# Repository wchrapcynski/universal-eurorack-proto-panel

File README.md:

# 8HP Eurorack Proto Panel

An open-hardware, all-in-one 8HP Eurorack front-panel PCB designed for
solderless breadboard synth prototyping. Front-panel controls (pots, jacks,
switch, button, and LEDs) mount directly to the front of the PCB and break out
to labeled 2.54 mm (0.1 in) female headers on the back for quick jumper-wire
connections to a BusBoard BB400 breadboard.

Designed as the companion panel to the
[BB400 Eurorack Power Breakout](https://github.com/wchrapcynski/bb400-euro-power).

## Status

**v0.1** - Initial PCB revision complete (ERC and DRC clean). Awaiting physical
fabrication and hardware verification.

## Features

- **Standard 8HP Eurorack size:** 40.3 x 128.5 mm with Doepfer A-100 mounting
  holes (`H1`-`H4`)
- **All-in-one PCB faceplate:** No separate aluminum panel required
- **All through-hole (THT) assembly:** Beginner-friendly hand soldering
- **Clean 2-layer layout:** All signal routing on `F.Cu` with an unbroken `GND`
  ground plane on `B.Cu`
- **Labeled rear breakout headers:** `J5`, `J6`, and `J7` clearly marked on the
  back silkscreen so you can patch to a breadboard without checking the
  schematic
- **Breadboard sled mounts:** Two centered M3 holes (`H5`, `H6`) for bolting a
  perpendicular 3D-printed BB400 breadboard sled behind the panel

## Front Panel Controls

- 3x 100kB vertical 9 mm trimmer potentiometers (`RV1`-`RV3`)
- 4x 3.5 mm mono jacks (`J1`-`J4`, Thonkiconn / PJ398SM)
- 1x SPDT slide switch (`SW1`)
- 1x 6 mm momentary tactile push button (`SW2`)
- 2x 3 mm indicator LEDs (`D1`, `D2`) with built-in 2.2k current-limiting
  resistors (`R1`, `R2`) on the back

## Rear Header Pinout (`B.Cu`)

All breakout headers are 2.54 mm pitch vertical female sockets mounted on the
back of the board.

### `J5` (1x9 - Potentiometers)

| Pin | Net  | Description          |
|-----|------|----------------------|
| 1   | P1_1 | RV1 pin 1            |
| 2   | P1_W | RV1 wiper (pin 2)    |
| 3   | P1_3 | RV1 pin 3            |
| 4   | P2_1 | RV2 pin 1            |
| 5   | P2_W | RV2 wiper (pin 2)    |
| 6   | P2_3 | RV2 pin 3            |
| 7   | P3_1 | RV3 pin 1            |
| 8   | P3_W | RV3 wiper (pin 2)    |
| 9   | P3_3 | RV3 pin 3            |

### `J6` (1x7 - Switch, Button, LEDs)

| Pin | Net     | Description                            |
|-----|---------|----------------------------------------|
| 1   | SW1_A   | SPDT switch throw A                    |
| 2   | SW1_C   | SPDT switch common                     |
| 3   | SW1_B   | SPDT switch throw B                    |
| 4   | BTN_1   | Tactile button side 1                  |
| 5   | BTN_2   | Tactile button side 2                  |
| 6   | LED1_IN | LED D1 input (via 2.2k R1 to D1 -> GND)|
| 7   | LED2_IN | LED D2 input (via 2.2k R2 to D2 -> GND)|

### `J7` (1x6 - Jacks and Ground)

| Pin | Net    | Description      |
|-----|--------|------------------|
| 1   | J1_TIP | Jack J1 tip      |
| 2   | J2_TIP | Jack J2 tip      |
| 3   | J3_TIP | Jack J3 tip      |
| 4   | J4_TIP | Jack J4 tip      |
| 5   | GND    | Ground reference |
| 6   | GND    | Ground reference |

## Bill of Materials (BOM)

[Interactive BOM](https://wchrapcynski.github.io/universal-eurorack-proto-panel/bom/ibom.html)

| Ref     | Qty | Value / Part          | Footprint / Notes                                              |
|---------|-----|-----------------------|----------------------------------------------------------------|
| RV1-RV3 | 3   | 100kB                 | 9 mm vertical tall trimmer pot (Bourns PTV09A-1 compatible)    |
| J1-J4   | 4   | 3.5 mm mono jack      | QingPu WQP-PJ398SM (Thonkiconn), vertical                      |
| SW1     | 1   | SPDT slide switch     | C&K OS102011MS2Q (2.0 mm pin pitch, straight THT)              |
| SW2     | 1   | Tactile push button   | 6 x 6 mm standard 4-pin THT push button                        |
| D1, D2  | 2   | 3 mm LED              | Standard 3 mm THT LED (any color)                              |
| R1, R2  | 2   | 2.2k                  | 1/4W axial resistor, 7.62 mm pitch (mounted on back)           |
| J5      | 1   | 1x9 female header     | 2.54 mm vertical pin socket (mounted on back)                  |
| J6      | 1   | 1x7 female header     | 2.54 mm vertical pin socket (mounted on back)                  |
| J7      | 1   | 1x6 female header     | 2.54 mm vertical pin socket (mounted on back)                  |

## Fabrication

- Designed in **KiCad 10**
- 2-layer PCB, 1.6 mm FR-4, 1 oz copper
- Dimensions: 40.3 x 128.5 mm (8HP)
- Can be ordered directly from OSH Park by uploading the `.kicad_pcb` file, or
  fabricated anywhere using standard Gerber + drill exports

## 3D-Printed BB400 Breadboard Sled

The repository includes a perpendicular breadboard sled that bolts to the back
of the PCB at `H5` and `H6` (`98.0 mm` apart) and holds a BusBoard BB400
(`84 x 54 x 9 mm`) cleanly inside the 8HP width and 3U rail clearance.

### Files

- `baseplate.FCStd` - FreeCAD 1.1 source file
- `baseplate.stl` - Ready-to-slice 3D-printable STL

### Dimensions and Printing

- **Size:** 65 mm deep x 106 mm tall x 3 mm thick wall (24 mm total width with
  mounting tabs)
- **Clearances:** 5 mm front recess between the two tabs clears `R1` and rear
  solder joints; 65 mm depth leaves room for `J5` jumper wires while fitting
  inside shallow cases (tested against a 70 mm deep Apache 2800 Eurorack case)
- **Orientation:** Print flat on the build plate (tabs pointing up), **no
  supports required**
- **Hardware:** 2x M3 screws (8 mm or 10 mm) and 2x standard M3 hex nuts
  (press-fit into the rear 2.6 mm hex pockets)

## License

Copyright (c) 2026 William Chrapcynski

This hardware design is licensed under the Creative Commons
Attribution-NonCommercial-ShareAlike 4.0 International License
(**CC BY-NC-SA 4.0**). See https://creativecommons.org/licenses/by-nc-sa/4.0/
for details.

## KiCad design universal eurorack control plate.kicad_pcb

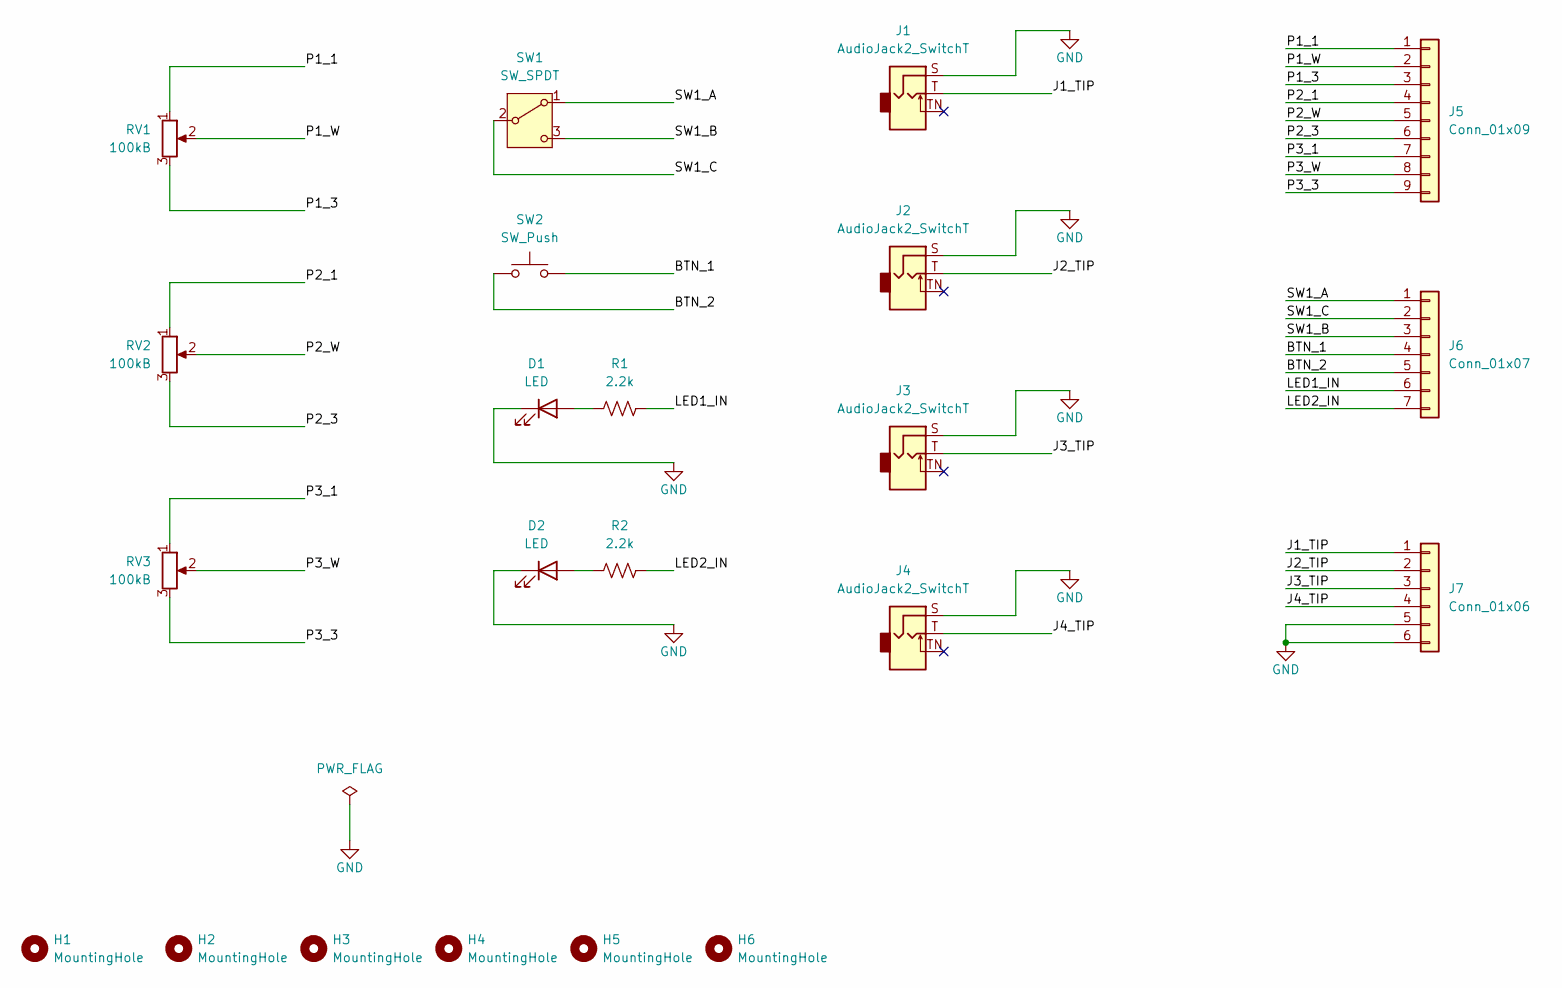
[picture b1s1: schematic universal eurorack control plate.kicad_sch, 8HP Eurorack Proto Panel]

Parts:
D1, D2: LED; LED_D3.0mm
H1, H2, H3, H4, H5, H6: MountingHole; MountingHole_3.2mm_M3
J1, J2, J3, J4: AudioJack2_SwitchT; Jack_3.5mm_QingPu_WQP-PJ398SM_Vertical_CircularHoles
J5: Conn_01x09; PinSocket_1x09_P2.54mm_Vertical
J6: Conn_01x07; PinSocket_1x07_P2.54mm_Vertical
J7: Conn_01x06; PinSocket_1x06_P2.54mm_Vertical
R1, R2: 2.2k; R_Axial_DIN0207_L6.3mm_D2.5mm_P7.62mm_Horizontal
RV1, RV2, RV3: 100kB; Potentiometer_Bourns_PTV09A-1_Single_Vertical
SW1: SW_SPDT; SW_Slide_SPDT_Straight_CK_OS102011MS2Q
SW2: SW_Push; SW_PUSH_6mm

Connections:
/BTN_1: J6.4, SW2.2
/BTN_2: J6.5, SW2.1
/J1_TIP: J1.T, J7.1
/J2_TIP: J2.T, J7.2
/J3_TIP: J3.T, J7.3
/J4_TIP: J4.T, J7.4
/LED1_IN: J6.6, R1.2
/LED2_IN: J6.7, R2.2
/P1_1: J5.1, RV1.1
/P1_3: J5.3, RV1.3
/P1_W: J5.2, RV1.2
/P2_1: J5.4, RV2.1
/P2_3: J5.6, RV2.3
/P2_W: J5.5, RV2.2
/P3_1: J5.7, RV3.1
/P3_3: J5.9, RV3.3
/P3_W: J5.8, RV3.2
/SW1_A: J6.1, SW1.1 (A)
/SW1_B: J6.3, SW1.3 (C)
/SW1_C: J6.2, SW1.2 (B)
GND: D1.1 (K), D2.1 (K), J1.S, J2.S, J3.S, J4.S, J7.5, J7.6
unnamed: D1.2 (A), R1.1
unnamed: D2.2 (A), R2.1

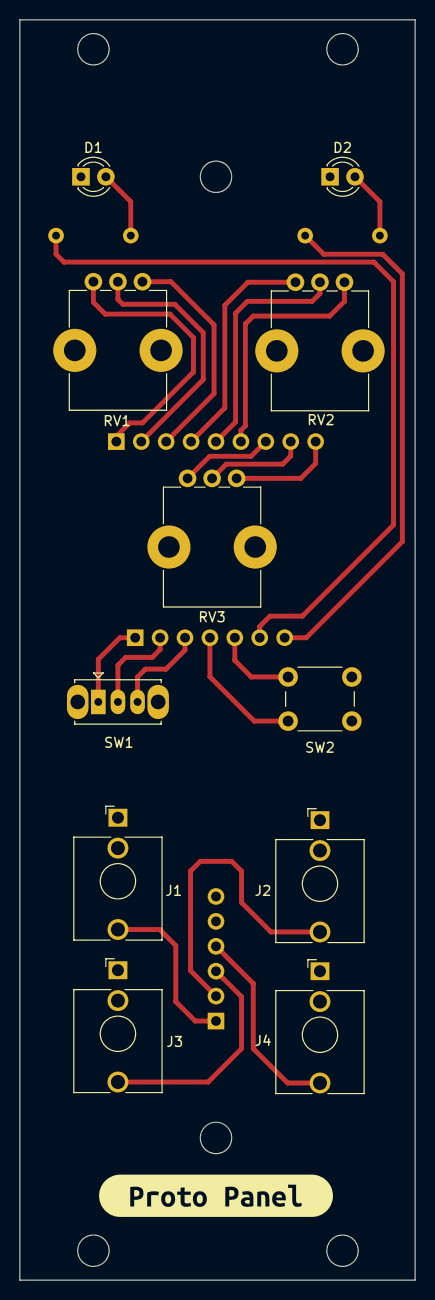
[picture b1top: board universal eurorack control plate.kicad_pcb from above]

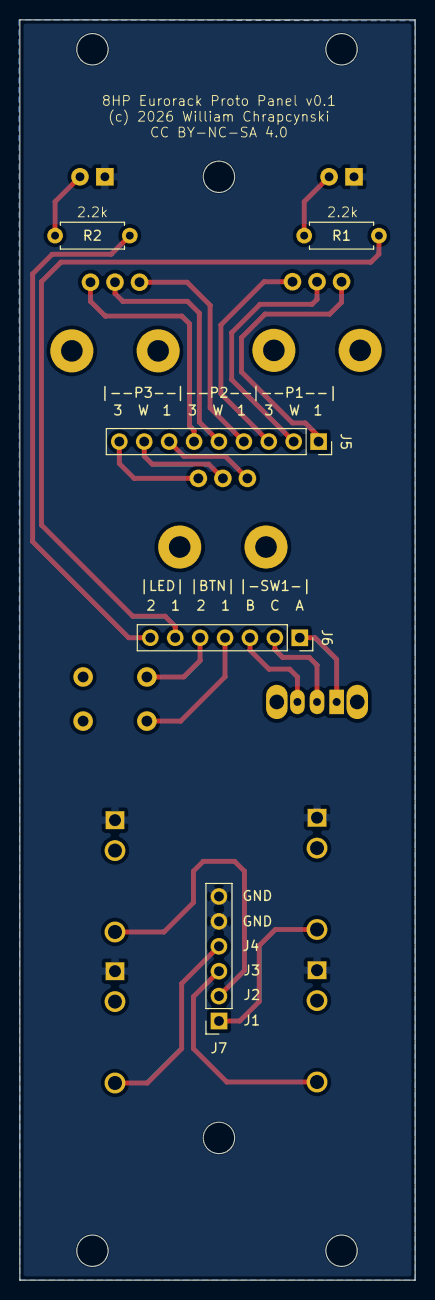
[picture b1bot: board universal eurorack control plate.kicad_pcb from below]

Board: 2 copper layers, 40.3 x 128.5 mm, 23 parts (5 on the bottom side), 23 nets.

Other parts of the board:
kibuzzard-6B0A11B3: G***; kibuzzard-6B0A11B3
